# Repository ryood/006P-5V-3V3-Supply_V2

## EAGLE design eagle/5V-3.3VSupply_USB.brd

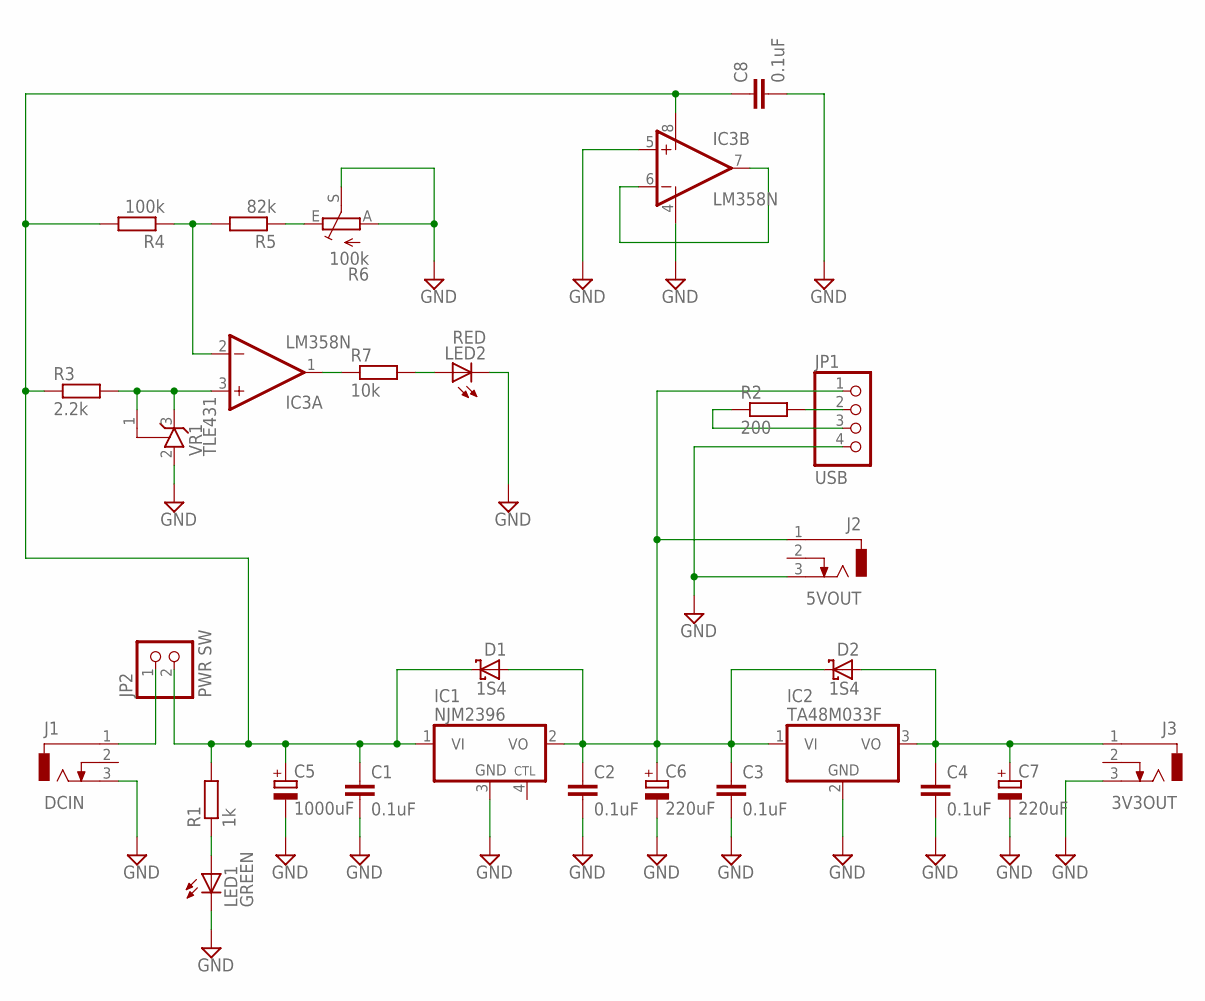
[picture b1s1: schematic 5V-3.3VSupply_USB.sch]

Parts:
C1, C2, C3, C4, C8: 0.1uF; C025-024X044
C5: 1000uF; TT5D11L
C6, C7: 220uF; E5-8,5
D1, D2: 1S4; DO41-7.6
IC1: NJM2396; TO220-4H
IC2: TA48M033F; TO220V
IC3: LM358N; DIL08
J1: DCIN; DCJ0303
J2: 5VOUT; DCJ0303
J3: 3V3OUT; DCJ0303
JP1: USB; 1X04
JP2: PWR SW; 1X02
LED1: GREEN; LED3MM
LED2: RED; LED3MM
R1: 1k; 0207/7
R2: 200; 0207/2V
R3: 2.2k; 0207/7
R4: 100k; 0207/7
R5: 82k; 0207/7
R6: 100k; CT6
R7: 10k; 0207/7
VR1: TLE431; TO226AA

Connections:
GND: C1.2, C2.2, C3.2, C4.2, C5.-, C6.-, C7.-, C8.2, IC1.3 (GND), IC2.2 (GND), IC3.4 (V-), IC3.5 (+IN), J1.3, J2.3, J3.3, JP1.4, LED1.K (C), LED2.K (C), R6.A, R6.S, VR1.2 (A)
unnamed: C1.1, C5.+, C8.1, D1.C, IC1.1 (VI), IC3.8 (V+), JP2.2, R1.2, R3.1, R4.2
unnamed: C2.1, C3.1, C6.+, D1.A, D2.C, IC1.2 (VO), IC2.1 (VI), J2.1, JP1.1
unnamed: C4.1, C7.+, D2.A, IC2.3 (VO), J3.1
unnamed: LED1.A, R1.1
unnamed: J1.1, JP2.1
unnamed: JP1.2, R2.2
unnamed: JP1.3, R2.1
unnamed: IC3.3 (+IN), R3.2, VR1.1 (R), VR1.3 (C)
unnamed: IC3.2 (-IN), R4.1, R5.2
unnamed: R5.1, R6.E
unnamed: IC3.1 (OUT), R7.1
unnamed: LED2.A, R7.2
unnamed: IC3.6 (-IN), IC3.7 (OUT)

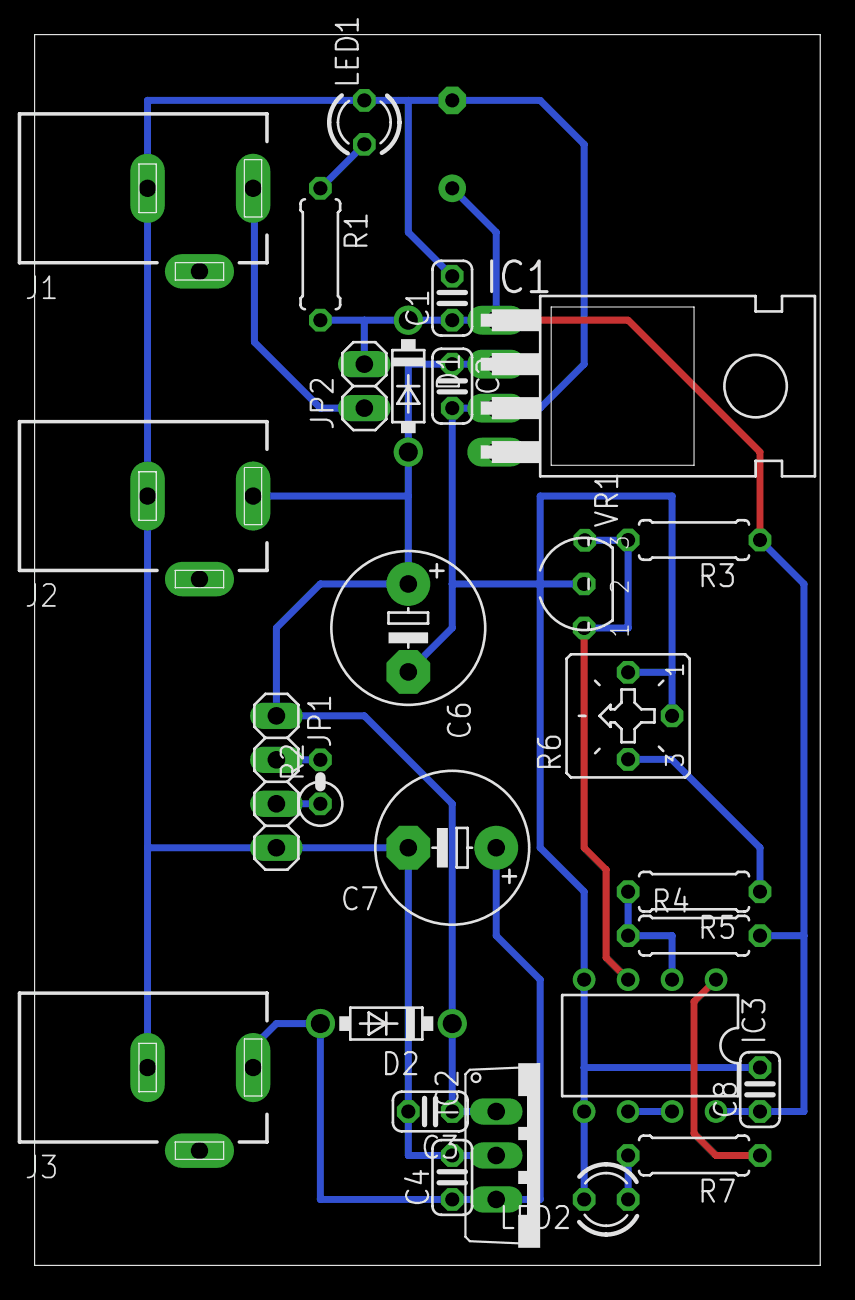
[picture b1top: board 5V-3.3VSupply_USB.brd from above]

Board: 2 copper layers, 45.4 x 71.1 mm, 28 parts (1 on the bottom side), 14 nets.

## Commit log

2016-03-20 基板図配置修正
2016-03-20 基板図修正
2016-03-20 コンパレーターの入力の正負を入れ替え
2016-03-20 画像、テスト表追加
2016-03-24 Add: Case Design
